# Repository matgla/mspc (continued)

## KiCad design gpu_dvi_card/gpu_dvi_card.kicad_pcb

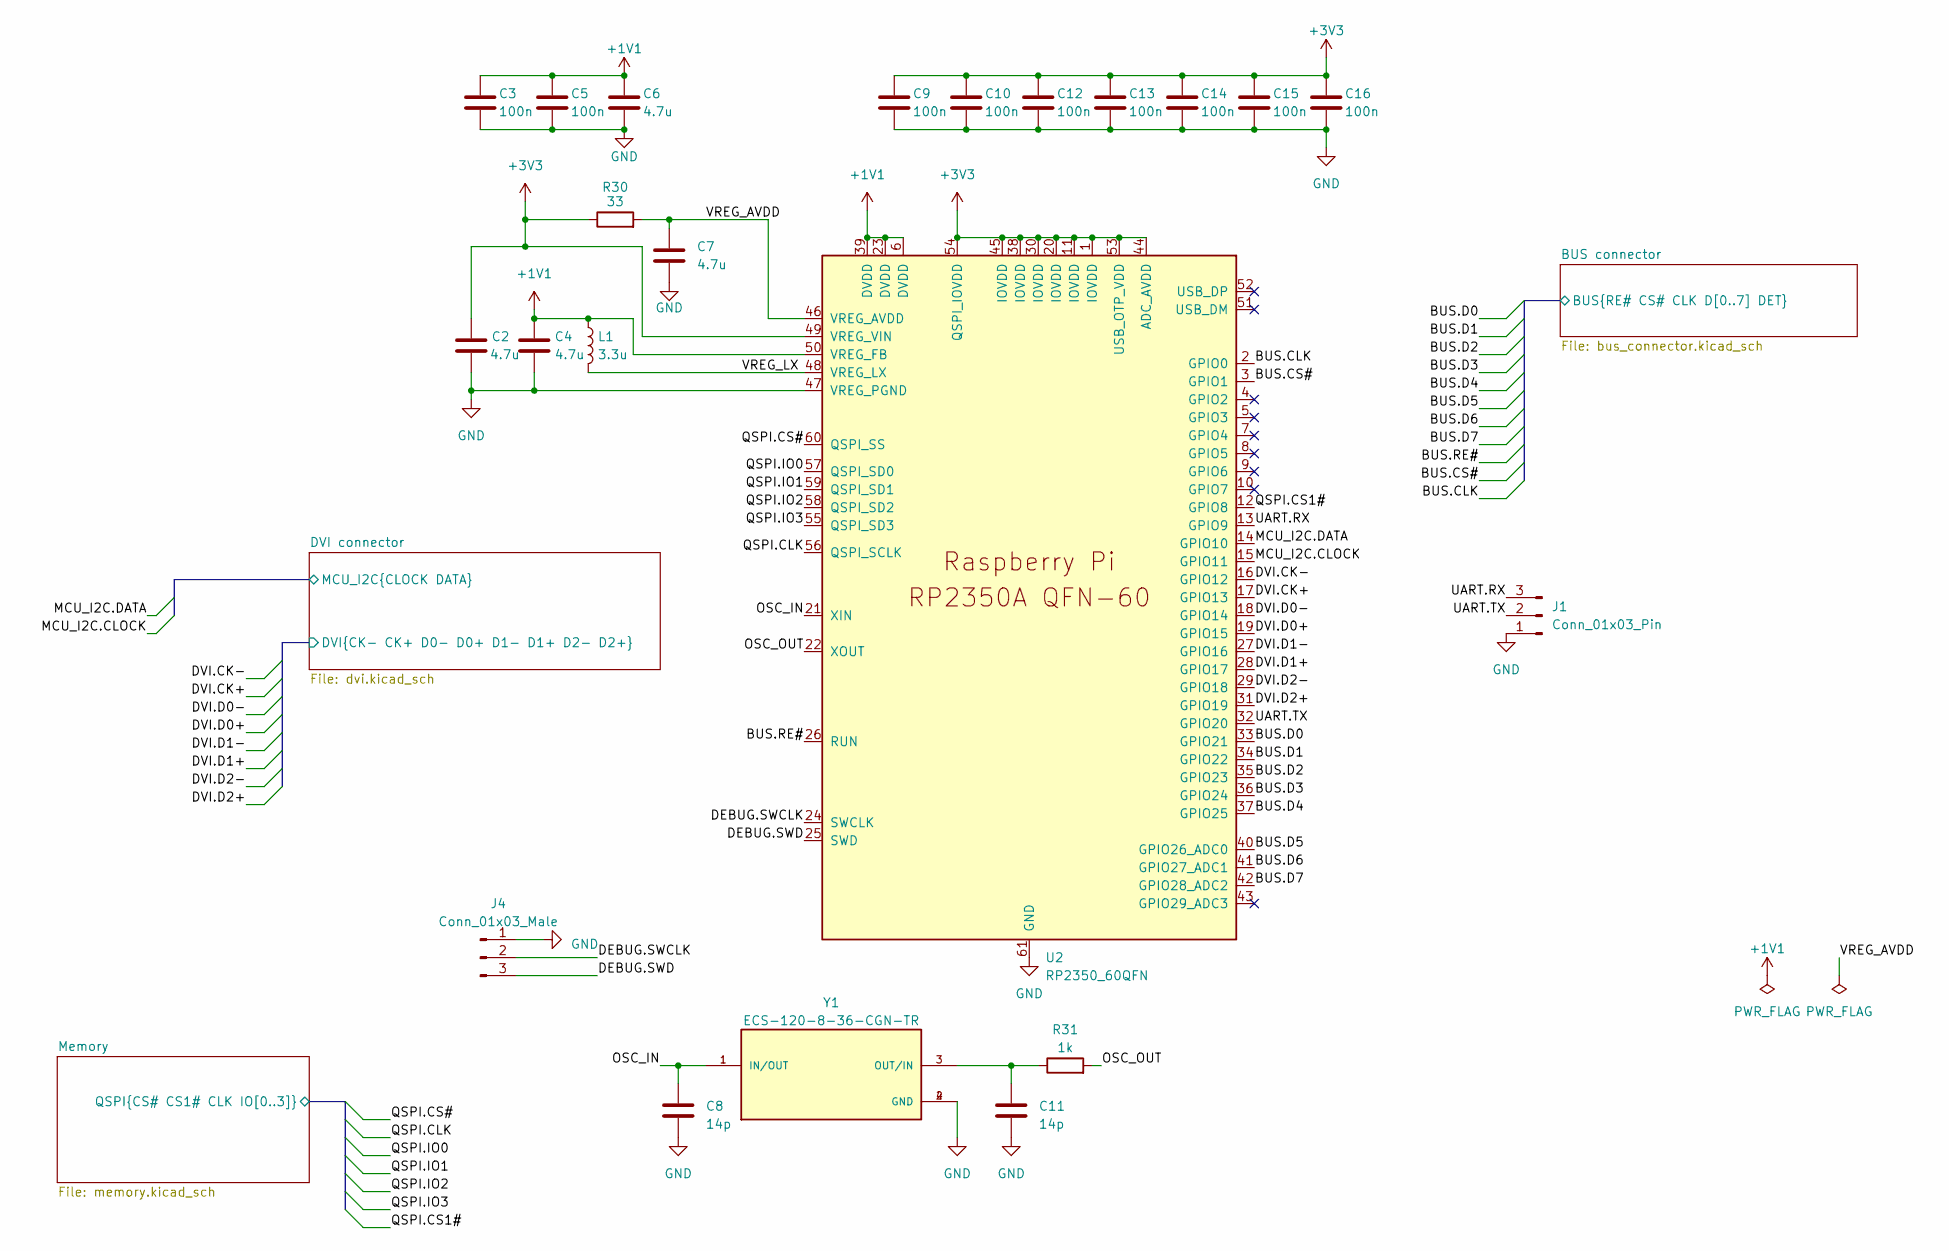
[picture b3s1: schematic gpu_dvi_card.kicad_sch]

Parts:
C2, C4, C6, C7: 4.7u; C_0402_1005Metric_Pad0.74x0.62mm_HandSolder
C3, C5, C9, C10, C12, C13, C14, C15, C16: 100n; C_0402_1005Metric_Pad0.74x0.62mm_HandSolder
C8, C11: 14p; C_0402_1005Metric_Pad0.74x0.62mm_HandSolder
J1: Conn_01x03_Pin; PinHeader_1x03_P2.54mm_Vertical
J4: Conn_01x03_Male; PinHeader_1x03_P2.54mm_Vertical
L1: 3.3u; L_0805_2012Metric_Pad1.15x1.40mm_HandSolder
R30: 33; R_0402_1005Metric_Pad0.72x0.64mm_HandSolder
R31: 1k; R_0402_1005Metric_Pad0.72x0.64mm_HandSolder
U2: RP2350_60QFN; RP2350-QFN-60-1EP_7x7_P0.4mm_EP3.4x3.4mm_ThermalVias
Y1: ECS-120-8-36-CGN-TR; XTAL_ECS-120-8-36-CGN-TR; PARTREV 2017

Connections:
+1V1: C3.1, C4.1, C5.1, C6.1, L1.1, U2.6 (DVDD), U2.23 (DVDD), U2.39 (DVDD), U2.50 (VREG_FB)
+3V3: C2.1, C9.1, C10.1, C12.1, C13.1, C14.1, C15.1, C16.1, R30.1, U2.1 (IOVDD), U2.11 (IOVDD), U2.20 (IOVDD), U2.30 (IOVDD), U2.38 (IOVDD), U2.44 (ADC_AVDD), U2.45 (IOVDD), U2.49 (VREG_VIN), U2.53 (USB_OTP_VDD), U2.54 (QSPI_IOVDD); also elsewhere on the board
/BUS connector/BUS.CLK: U2.2 (GPIO0); also elsewhere on the board
/BUS connector/BUS.CS#: U2.3 (GPIO1); also elsewhere on the board
/BUS connector/BUS.D0: U2.33 (GPIO21); also elsewhere on the board
/BUS connector/BUS.D1: U2.34 (GPIO22); also elsewhere on the board
/BUS connector/BUS.D2: U2.35 (GPIO23); also elsewhere on the board
/BUS connector/BUS.D3: U2.36 (GPIO24); also elsewhere on the board
/BUS connector/BUS.D4: U2.37 (GPIO25); also elsewhere on the board
/BUS connector/BUS.D5: U2.40 (GPIO26_ADC0); also elsewhere on the board
/BUS connector/BUS.D6: U2.41 (GPIO27_ADC1); also elsewhere on the board
/BUS connector/BUS.D7: U2.42 (GPIO28_ADC2); also elsewhere on the board
/BUS connector/BUS.RE#: U2.26 (RUN); also elsewhere on the board
/DEBUG.SWCLK: J4.2, U2.24 (SWCLK)
/DEBUG.SWD: J4.3, U2.25 (SWD)
/DVI connector/DVI.CK+: U2.17 (GPIO13); also elsewhere on the board
/DVI connector/DVI.CK-: U2.16 (GPIO12); also elsewhere on the board
/DVI connector/DVI.D0+: U2.19 (GPIO15); also elsewhere on the board
/DVI connector/DVI.D0-: U2.18 (GPIO14); also elsewhere on the board
/DVI connector/DVI.D1+: U2.28 (GPIO17); also elsewhere on the board
/DVI connector/DVI.D1-: U2.27 (GPIO16); also elsewhere on the board
/DVI connector/DVI.D2+: U2.31 (GPIO19); also elsewhere on the board
/DVI connector/DVI.D2-: U2.29 (GPIO18); also elsewhere on the board
/DVI connector/MCU_I2C.CLOCK: U2.15 (GPIO11); also elsewhere on the board
/DVI connector/MCU_I2C.DATA: U2.14 (GPIO10); also elsewhere on the board
/Memory/QSPI.CLK: U2.56 (QSPI_SCLK); also elsewhere on the board
/Memory/QSPI.CS1#: U2.12 (GPIO8); also elsewhere on the board
/Memory/QSPI.CS#: U2.60 (QSPI_SS); also elsewhere on the board
/Memory/QSPI.IO0: U2.57 (QSPI_SD0); also elsewhere on the board
/Memory/QSPI.IO1: U2.59 (QSPI_SD1); also elsewhere on the board
/Memory/QSPI.IO2: U2.58 (QSPI_SD2); also elsewhere on the board
/Memory/QSPI.IO3: U2.55 (QSPI_SD3); also elsewhere on the board
/OSC_IN: C8.1, U2.21 (XIN), Y1.1 (IN/OUT)
/OSC_OUT: R31.2, U2.22 (XOUT)
/UART.RX: J1.3, U2.13 (GPIO9)
/UART.TX: J1.2, U2.32 (GPIO20)
/VREG_AVDD: C7.1, R30.2, U2.46 (VREG_AVDD)
/VREG_LX: L1.2, U2.48 (VREG_LX)
GND: C2.2, C3.2, C4.2, C5.2, C6.2, C7.2, C8.2, C9.2, C10.2, C11.2, C12.2, C13.2, C14.2, C15.2, C16.2, J1.1, J4.1, U2.47 (VREG_PGND), U2.61 (GND), Y1.2 (GND), Y1.4 (GND); also elsewhere on the board
unnamed: C11.1, R31.1, Y1.3 (OUT/IN)

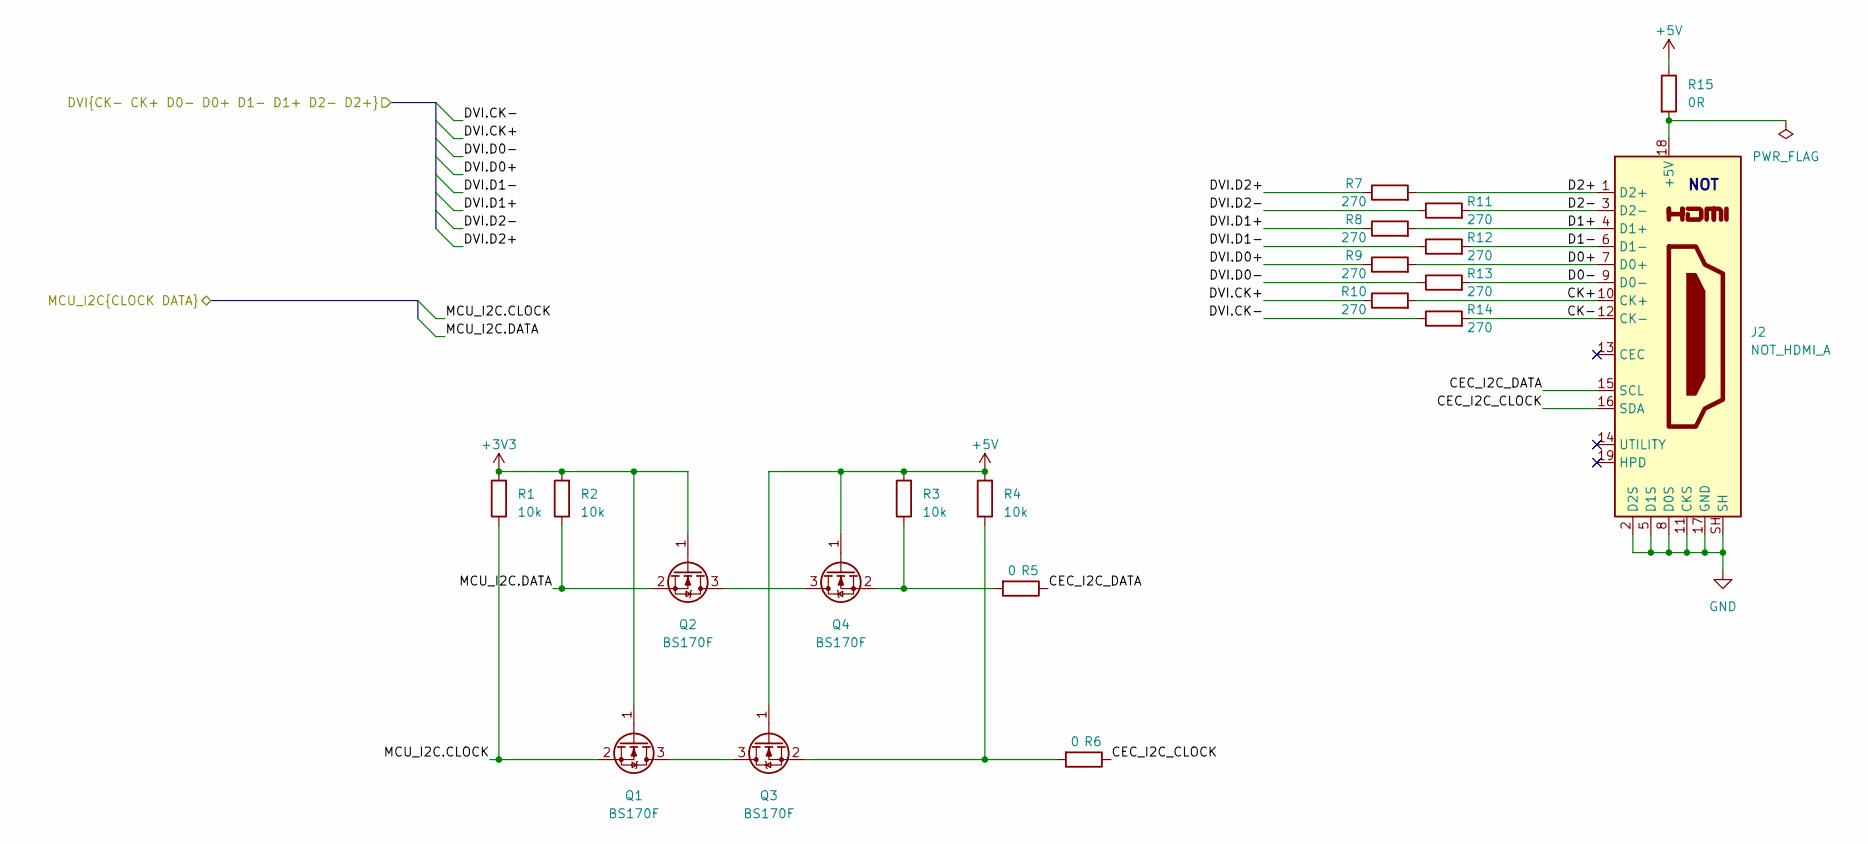
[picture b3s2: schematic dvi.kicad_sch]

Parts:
J2: NOT_HDMI_A; HDMI_A_Molex_208658-1001_Horizontal
Q1, Q2, Q3, Q4: BS170F; SOT-23
R1, R2, R3, R4: 10k; R_0402_1005Metric_Pad0.72x0.64mm_HandSolder
R5, R6: 0; R_0402_1005Metric_Pad0.72x0.64mm_HandSolder
R7, R8, R9, R10, R11, R12, R13, R14: 270; R_0402_1005Metric_Pad0.72x0.64mm_HandSolder
R15: 0R; R_0402_1005Metric_Pad0.72x0.64mm_HandSolder

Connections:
+3V3: Q1.1 (G), Q2.1 (G), R1.2, R2.2; also elsewhere on the board
+5V: Q3.1 (G), Q4.1 (G), R3.2, R4.2, R15.1; also elsewhere on the board
/DVI connector/CEC_I2C_CLOCK: J2.16 (SDA), R6.1
/DVI connector/CEC_I2C_DATA: J2.15 (SCL), R5.1
/DVI connector/CK+: J2.10 (CK+), R10.2
/DVI connector/CK-: J2.12 (CK-), R14.2
/DVI connector/D0+: J2.7 (D0+), R9.2
/DVI connector/D0-: J2.9 (D0-), R13.2
/DVI connector/D1+: J2.4 (D1+), R8.2
/DVI connector/D1-: J2.6 (D1-), R12.2
/DVI connector/D2+: J2.1 (D2+), R7.2
/DVI connector/D2-: J2.3 (D2-), R11.2
/DVI connector/DVI.CK+: R10.1; also elsewhere on the board
/DVI connector/DVI.CK-: R14.1; also elsewhere on the board
/DVI connector/DVI.D0+: R9.1; also elsewhere on the board
/DVI connector/DVI.D0-: R13.1; also elsewhere on the board
/DVI connector/DVI.D1+: R8.1; also elsewhere on the board
/DVI connector/DVI.D1-: R12.1; also elsewhere on the board
/DVI connector/DVI.D2+: R7.1; also elsewhere on the board
/DVI connector/DVI.D2-: R11.1; also elsewhere on the board
/DVI connector/MCU_I2C.CLOCK: Q1.2 (S), R1.1; also elsewhere on the board
/DVI connector/MCU_I2C.DATA: Q2.2 (S), R2.1; also elsewhere on the board
GND: J2.2 (D2S), J2.5 (D1S), J2.8 (D0S), J2.11 (CKS), J2.17 (GND), J2.SH; also elsewhere on the board
unnamed: J2.18 (+5V), R15.2
unnamed: Q1.3 (D), Q3.3 (D)
unnamed: Q2.3 (D), Q4.3 (D)
unnamed: Q3.2 (S), R4.1, R6.2
unnamed: Q4.2 (S), R3.1, R5.2

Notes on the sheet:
NOT

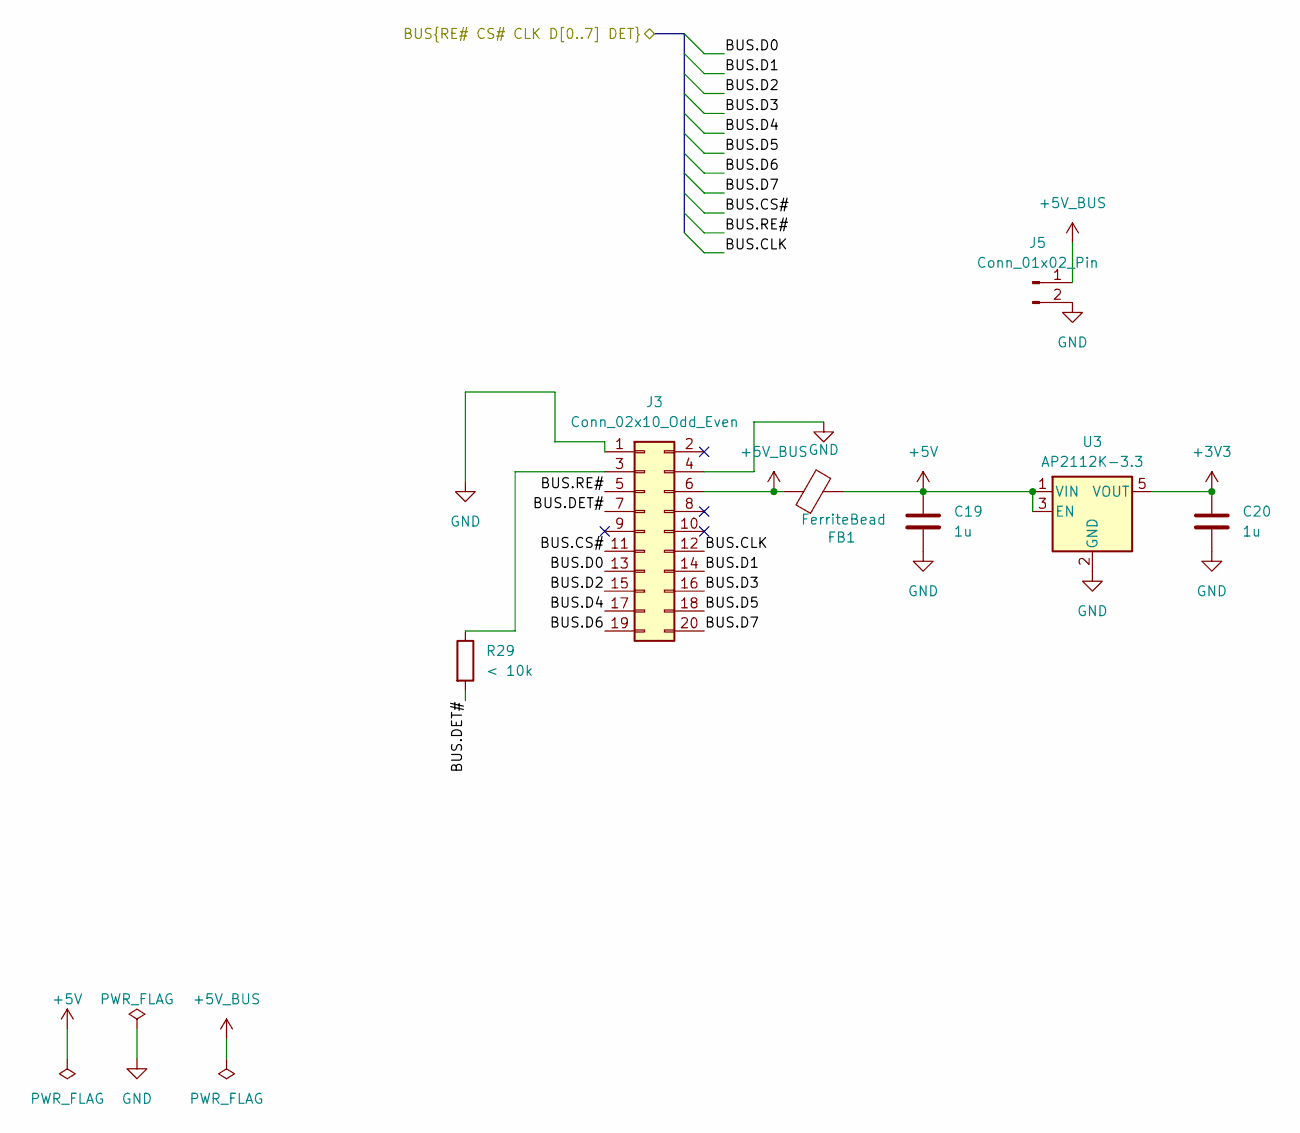
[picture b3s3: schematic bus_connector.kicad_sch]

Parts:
C19, C20: 1u; C_0402_1005Metric_Pad0.74x0.62mm_HandSolder
FB1: FerriteBead; L_0805_2012Metric_Pad1.05x1.20mm_HandSolder
J3: Conn_02x10_Odd_Even; PinHeader_2x10_P1.27mm_Vertical_SMD
J5: Conn_01x02_Pin; PinHeader_1x02_P2.54mm_Vertical
R29: < 10k; R_0402_1005Metric_Pad0.72x0.64mm_HandSolder
U3: AP2112K-3.3; SOT-23-5_HandSoldering

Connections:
+3V3: C20.1, U3.5 (VOUT); also elsewhere on the board
+5V: C19.1, FB1.2, U3.1 (VIN), U3.3 (EN); also elsewhere on the board
+5V_BUS: FB1.1, J3.6, J5.1
/BUS connector/BUS.CLK: J3.12; also elsewhere on the board
/BUS connector/BUS.CS#: J3.11; also elsewhere on the board
/BUS connector/BUS.D0: J3.13; also elsewhere on the board
/BUS connector/BUS.D1: J3.14; also elsewhere on the board
/BUS connector/BUS.D2: J3.15; also elsewhere on the board
/BUS connector/BUS.D3: J3.16; also elsewhere on the board
/BUS connector/BUS.D4: J3.17; also elsewhere on the board
/BUS connector/BUS.D5: J3.18; also elsewhere on the board
/BUS connector/BUS.D6: J3.19; also elsewhere on the board
/BUS connector/BUS.D7: J3.20; also elsewhere on the board
/BUS connector/BUS.DET#: J3.7, R29.2
/BUS connector/BUS.RE#: J3.5; also elsewhere on the board
GND: C19.2, C20.2, J3.1, J3.4, J5.2, U3.2 (GND); also elsewhere on the board
unnamed: J3.3, R29.1

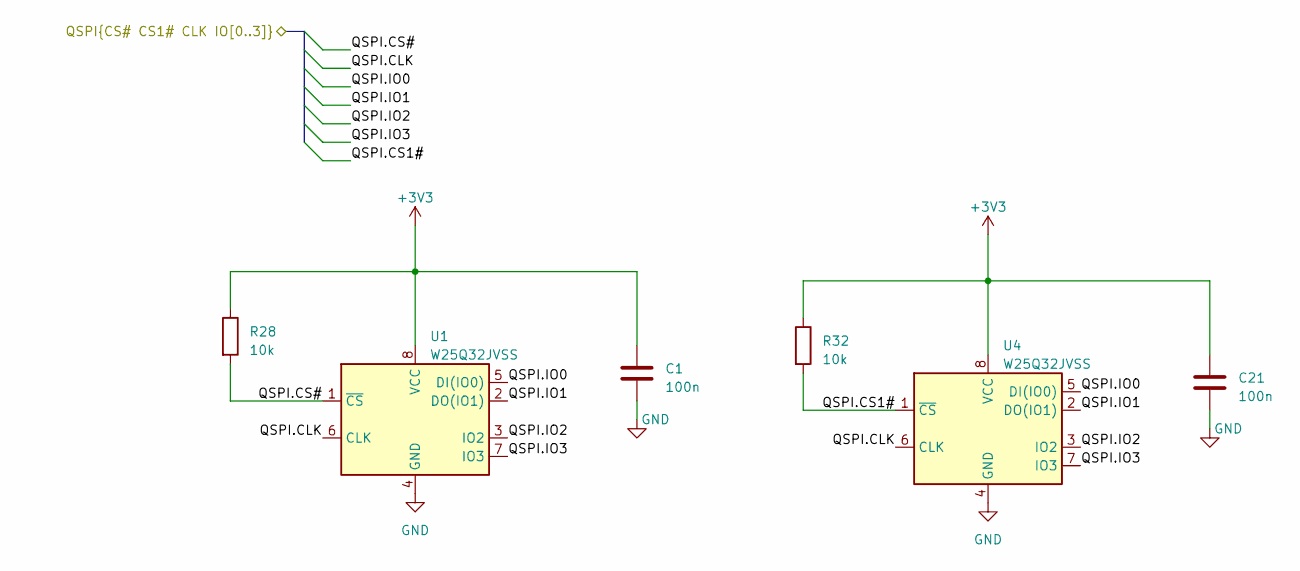
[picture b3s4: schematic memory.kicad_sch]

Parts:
C1, C21: 100n; C_0402_1005Metric_Pad0.74x0.62mm_HandSolder
R28, R32: 10k; R_0402_1005Metric_Pad0.72x0.64mm_HandSolder
U1, U4: W25Q32JVSS; SOIC-8_5.23x5.23mm_P1.27mm

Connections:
+3V3: C1.1, C21.1, R28.1, R32.1, U1.8 (VCC), U4.8 (VCC); also elsewhere on the board
/Memory/QSPI.CLK: U1.6 (CLK), U4.6 (CLK); also elsewhere on the board
/Memory/QSPI.CS1#: R32.2, U4.1 (~CS); also elsewhere on the board
/Memory/QSPI.CS#: R28.2, U1.1 (~CS); also elsewhere on the board
/Memory/QSPI.IO0: U1.5 (DI(IO0)), U4.5 (DI(IO0)); also elsewhere on the board
/Memory/QSPI.IO1: U1.2 (DO(IO1)), U4.2 (DO(IO1)); also elsewhere on the board
/Memory/QSPI.IO2: U1.3 (IO2), U4.3 (IO2); also elsewhere on the board
/Memory/QSPI.IO3: U1.7 (IO3), U4.7 (IO3); also elsewhere on the board
GND: C1.2, C21.2, U1.4 (GND), U4.4 (GND); also elsewhere on the board

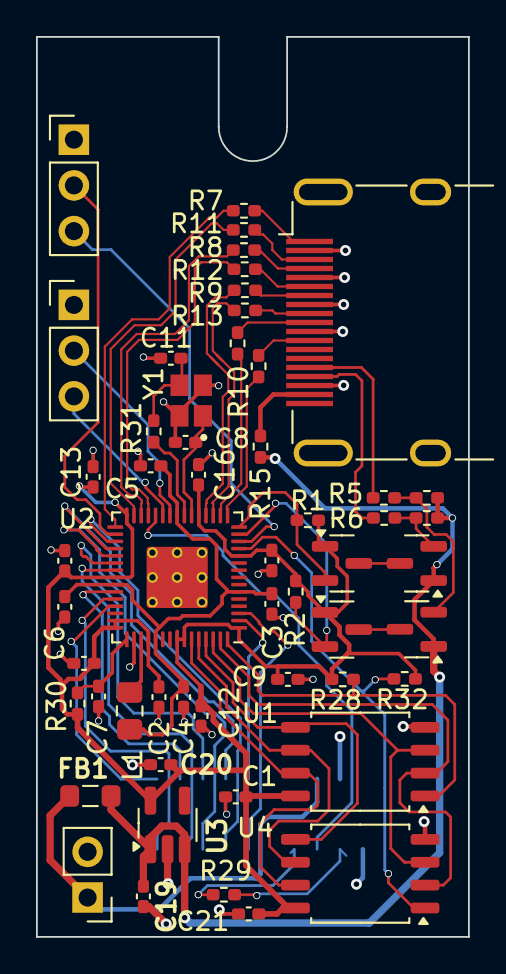
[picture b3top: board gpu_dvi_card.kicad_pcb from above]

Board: 4 copper layers, 24.0 x 50.0 mm, 55 parts (1 on the bottom side), 59 nets.

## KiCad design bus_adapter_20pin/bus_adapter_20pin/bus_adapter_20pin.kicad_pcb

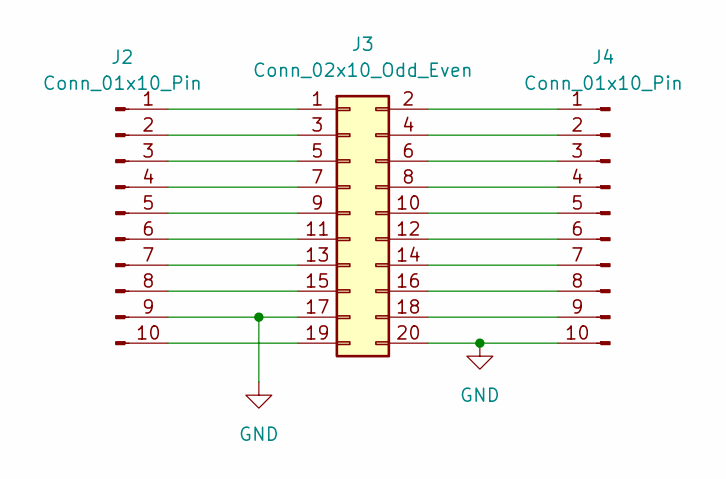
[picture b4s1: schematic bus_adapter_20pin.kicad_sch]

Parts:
J2, J4: Conn_01x10_Pin; PinHeader_1x10_P2.54mm_Vertical
J3: Conn_02x10_Odd_Even; PinHeader_2x10_P1.27mm_Vertical_SMD

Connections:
GND: J2.9, J3.17, J3.20, J4.10
unnamed: J2.1, J3.1
unnamed: J2.2, J3.3
unnamed: J2.3, J3.5
unnamed: J2.4, J3.7
unnamed: J2.5, J3.9
unnamed: J2.6, J3.11
unnamed: J2.7, J3.13
unnamed: J2.8, J3.15
unnamed: J2.10, J3.19
unnamed: J3.2, J4.1
unnamed: J3.4, J4.2
unnamed: J3.6, J4.3
unnamed: J3.8, J4.4
unnamed: J3.10, J4.5
unnamed: J3.12, J4.6
unnamed: J3.14, J4.7
unnamed: J3.16, J4.8
unnamed: J3.18, J4.9

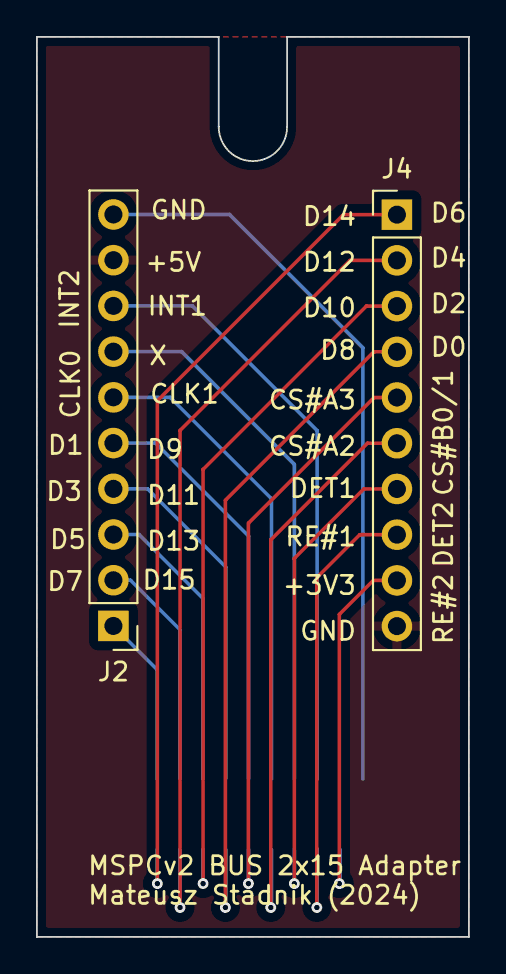
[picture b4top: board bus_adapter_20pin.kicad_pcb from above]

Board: 2 copper layers, 24.0 x 50.0 mm, 3 parts (1 on the bottom side), 19 nets.

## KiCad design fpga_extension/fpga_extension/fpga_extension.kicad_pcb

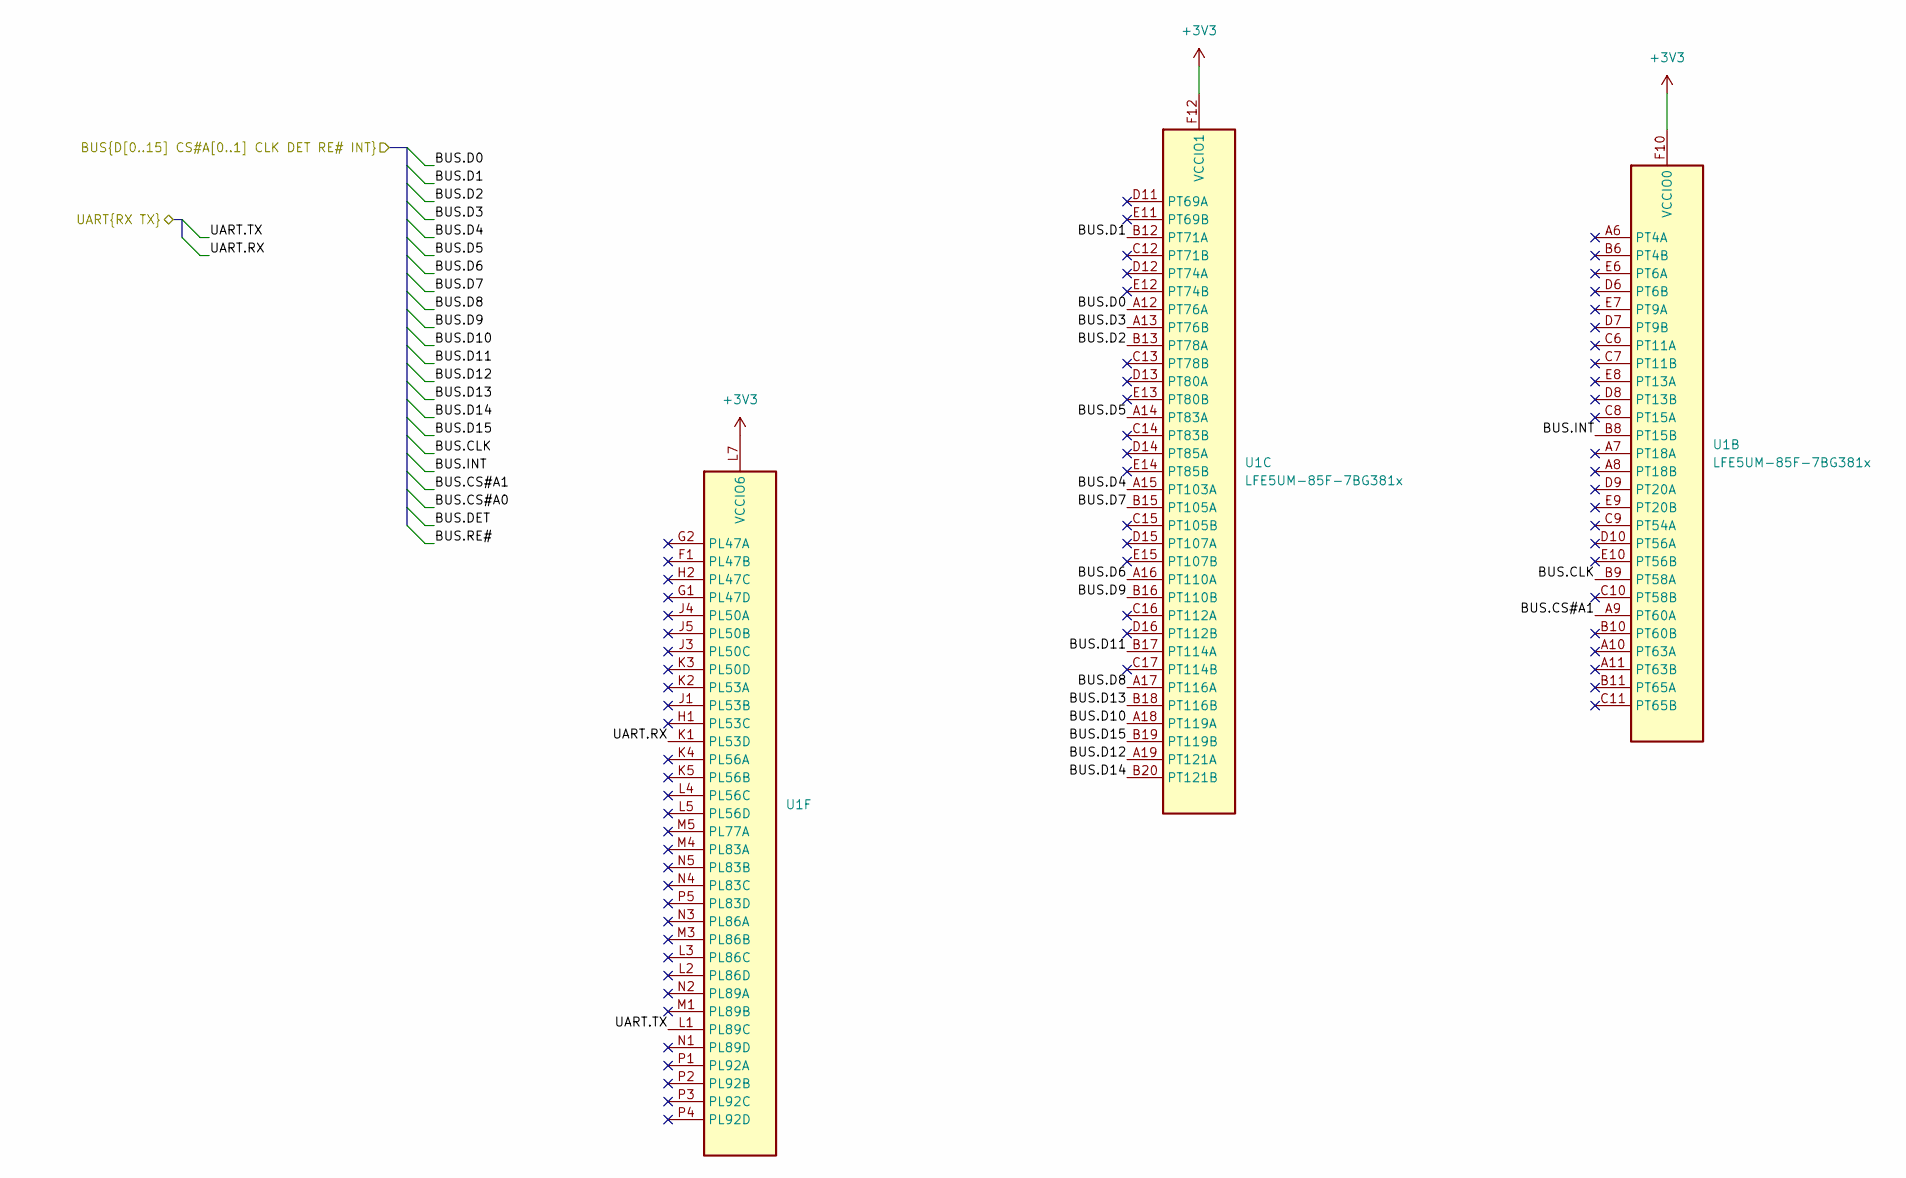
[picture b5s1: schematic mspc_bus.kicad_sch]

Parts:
U1: LFE5UM-85F-7BG381x; Lattice_caBGA-381_17.0x17.0mm_Layout20x20_P0.8mm_Ball0.4mm_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

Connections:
+3V3: U1.F9 (VCCIO0), U1.F10 (VCCIO0), U1.F11 (VCCIO1), U1.F12 (VCCIO1), U1.L6 (VCCIO6), U1.L7 (VCCIO6), U1.M6 (VCCIO6); also elsewhere on the board
/Connector/BUS.CLK: U1.B9 (PT58A); also elsewhere on the board
/Connector/BUS.CS#A1: U1.A9 (PT60A); also elsewhere on the board
/Connector/BUS.D0: U1.A12 (PT76A); also elsewhere on the board
/Connector/BUS.D1: U1.B12 (PT71A); also elsewhere on the board
/Connector/BUS.D2: U1.B13 (PT78A); also elsewhere on the board
/Connector/BUS.D3: U1.A13 (PT76B); also elsewhere on the board
/Connector/BUS.D4: U1.A15 (PT103A); also elsewhere on the board
/Connector/BUS.D5: U1.A14 (PT83A); also elsewhere on the board
/Connector/BUS.D6: U1.A16 (PT110A); also elsewhere on the board
/Connector/BUS.D7: U1.B15 (PT105A); also elsewhere on the board
/Connector/BUS.D8: U1.A17 (PT116A); also elsewhere on the board
/Connector/BUS.D9: U1.B16 (PT110B); also elsewhere on the board
/Connector/BUS.D10: U1.A18 (PT119A); also elsewhere on the board
/Connector/BUS.D11: U1.B17 (PT114A); also elsewhere on the board
/Connector/BUS.D12: U1.A19 (PT121A); also elsewhere on the board
/Connector/BUS.D13: U1.B18 (PT116B); also elsewhere on the board
/Connector/BUS.D14: U1.B20 (PT121B); also elsewhere on the board
/Connector/BUS.D15: U1.B19 (PT119B); also elsewhere on the board
/Connector/BUS.INT: U1.B8 (PT15B); also elsewhere on the board
/JTAG/UART.RX: U1.K1 (PL53D); also elsewhere on the board
/JTAG/UART.TX: U1.L1 (PL89C); also elsewhere on the board

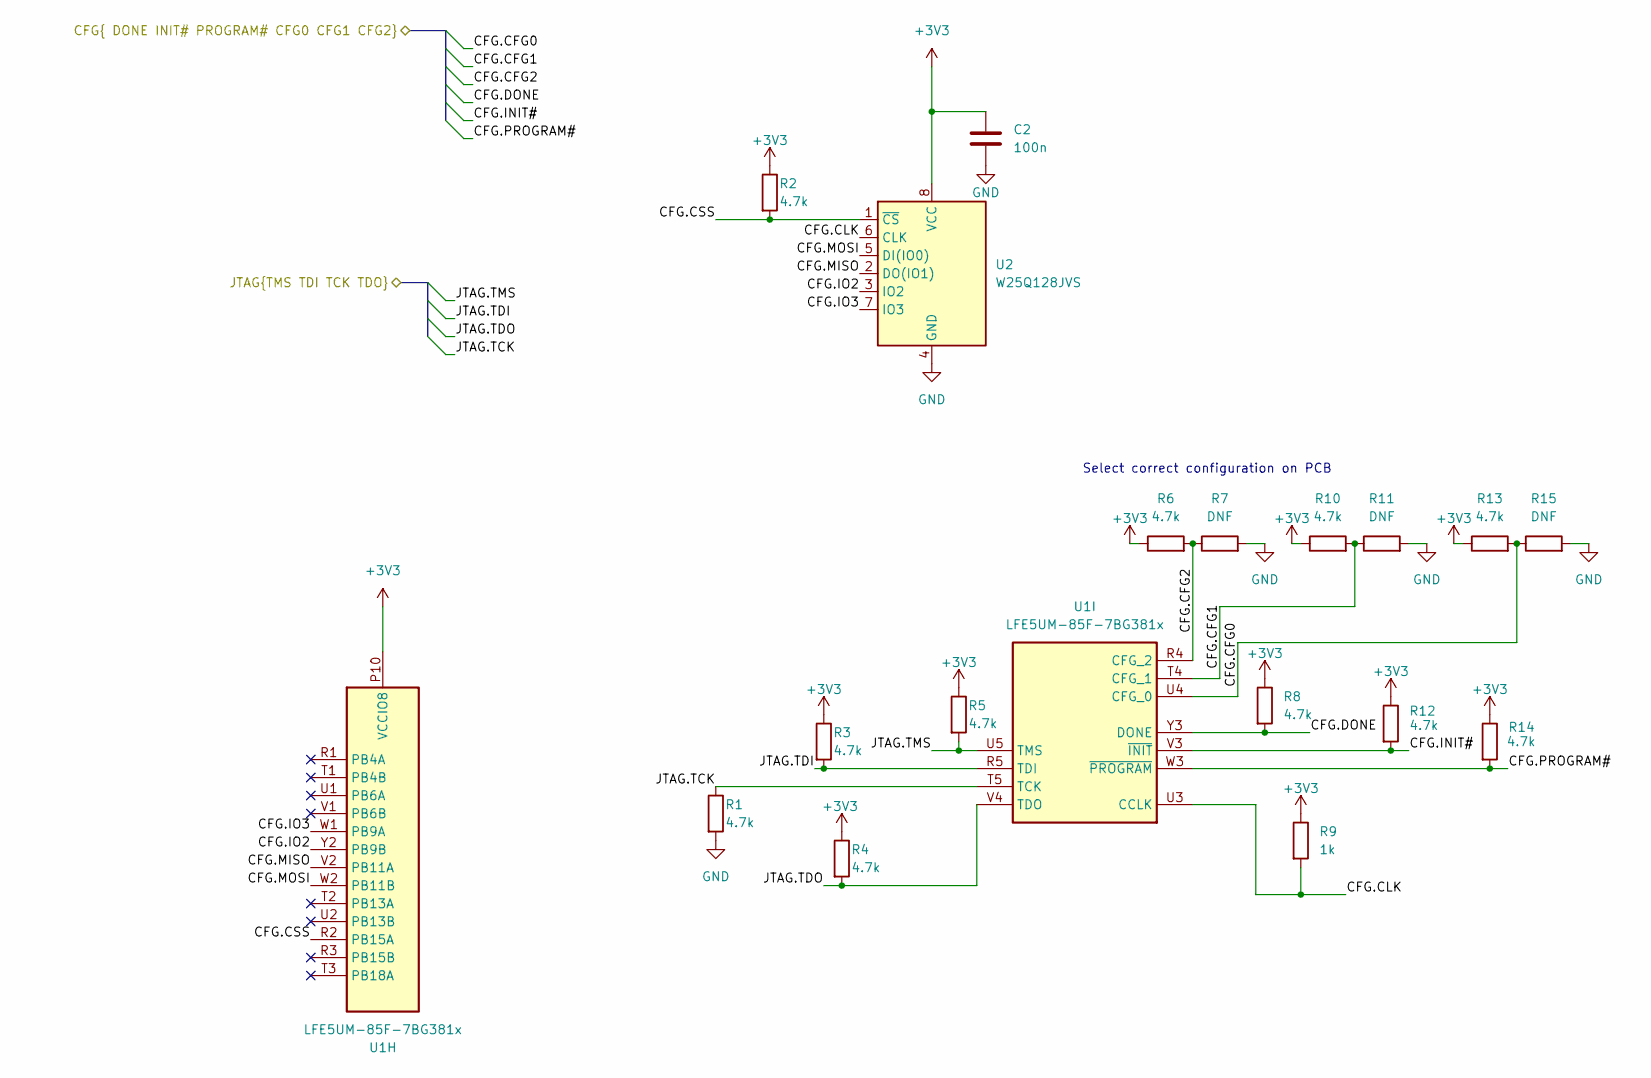
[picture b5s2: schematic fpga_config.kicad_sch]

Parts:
C2: 100n; C_0402_1005Metric_Pad0.74x0.62mm_HandSolder
R1, R2, R3, R4, R5, R6, R8, R10, R12, R13, R14: 4.7k; R_0402_1005Metric_Pad0.72x0.64mm_HandSolder
R7, R11, R15: DNF; R_0402_1005Metric_Pad0.72x0.64mm_HandSolder
R9: 1k; R_0402_1005Metric_Pad0.72x0.64mm_HandSolder
U1: LFE5UM-85F-7BG381x; Lattice_caBGA-381_17.0x17.0mm_Layout20x20_P0.8mm_Ball0.4mm_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
U2: W25Q128JVS; SOIC-8_5.23x5.23mm_P1.27mm

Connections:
+3V3: C2.1, R2.1, R3.1, R4.1, R5.1, R6.1, R8.1, R9.1, R10.1, R12.1, R13.1, R14.1, U1.P9 (VCCIO8), U1.P10 (VCCIO8), U2.8 (VCC); also elsewhere on the board
/FPGA Configuration/CFG.CFG0: R13.2, R15.1, U1.U4 (CFG_0); also elsewhere on the board
/FPGA Configuration/CFG.CFG1: R10.2, R11.1, U1.T4 (CFG_1); also elsewhere on the board
/FPGA Configuration/CFG.CFG2: R6.2, R7.1, U1.R4 (CFG_2); also elsewhere on the board
/FPGA Configuration/CFG.CLK: R9.2, U1.U3 (CCLK), U2.6 (CLK)
/FPGA Configuration/CFG.CSS: R2.2, U1.R2 (PB15A), U2.1 (~CS)
/FPGA Configuration/CFG.DONE: R8.2, U1.Y3 (DONE); also elsewhere on the board
/FPGA Configuration/CFG.INIT#: R12.2, U1.V3 (~INIT); also elsewhere on the board
/FPGA Configuration/CFG.IO2: U1.Y2 (PB9B), U2.3 (IO2)
/FPGA Configuration/CFG.IO3: U1.W1 (PB9A), U2.7 (IO3)
/FPGA Configuration/CFG.MISO: U1.V2 (PB11A), U2.2 (DO(IO1))
/FPGA Configuration/CFG.MOSI: U1.W2 (PB11B), U2.5 (DI(IO0))
/FPGA Configuration/CFG.PROGRAM#: R14.2, U1.W3 (~PROGRAM); also elsewhere on the board
/FPGA Configuration/JTAG.TCK: R1.1, U1.T5 (TCK); also elsewhere on the board
/FPGA Configuration/JTAG.TDI: R3.2, U1.R5 (TDI); also elsewhere on the board
/FPGA Configuration/JTAG.TDO: R4.2, U1.V4 (TDO); also elsewhere on the board
/FPGA Configuration/JTAG.TMS: R5.2, U1.U5 (TMS); also elsewhere on the board
GND: C2.2, R1.2, R7.2, R11.2, R15.2, U2.4 (GND); also elsewhere on the board

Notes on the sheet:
Select correct configuration on PCB

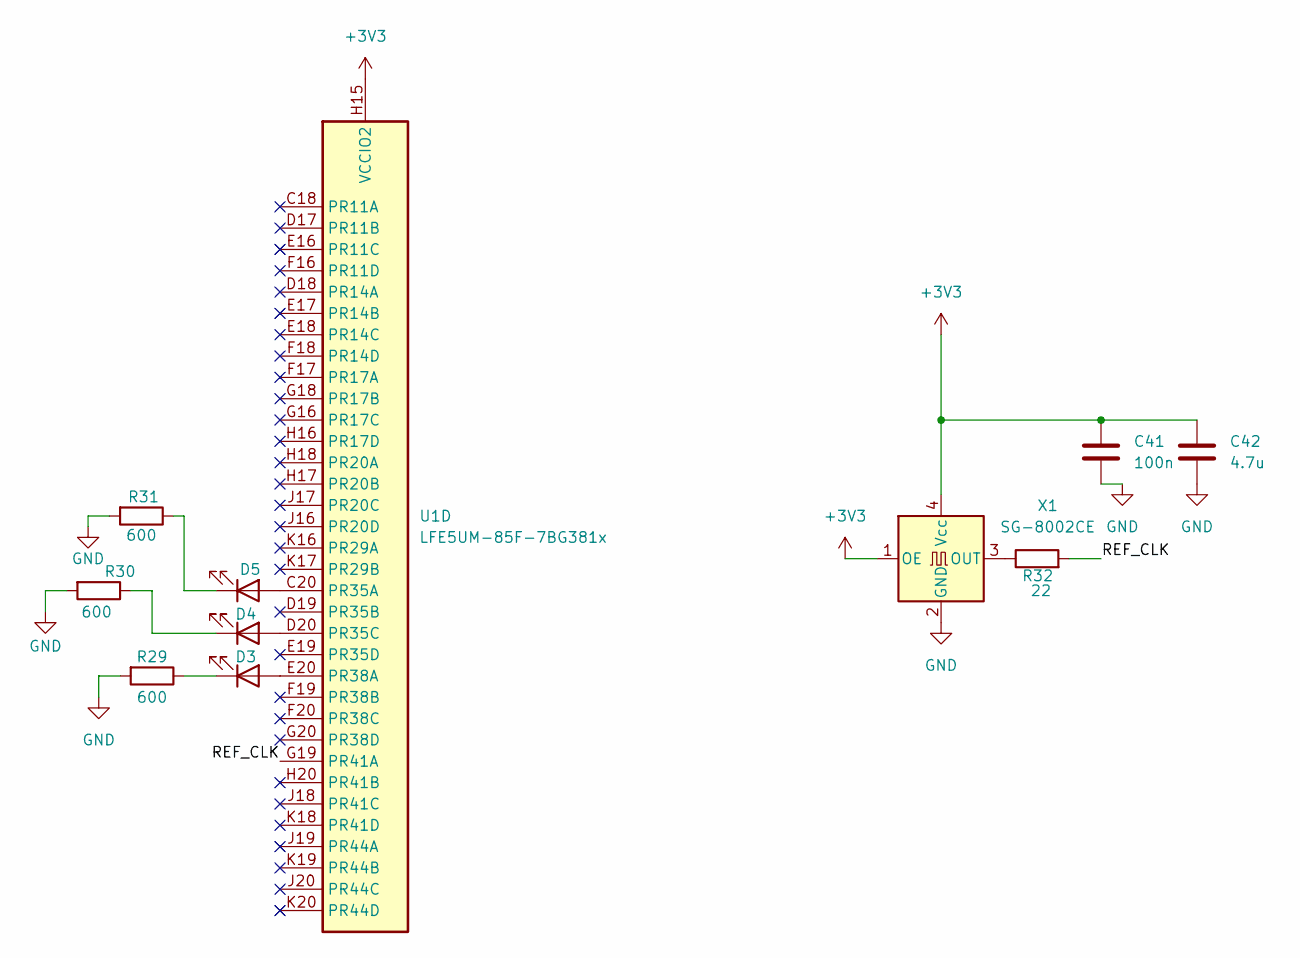
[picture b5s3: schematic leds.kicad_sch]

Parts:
C41: 100n; C_0402_1005Metric_Pad0.74x0.62mm_HandSolder
C42: 4.7u; C_0402_1005Metric_Pad0.74x0.62mm_HandSolder
D3, D4, D5: LED; LED_0402_1005Metric_Pad0.77x0.64mm_HandSolder
R29, R30, R31: 600; R_0402_1005Metric_Pad0.72x0.64mm_HandSolder
R32: 22; R_0402_1005Metric_Pad0.72x0.64mm_HandSolder
U1: LFE5UM-85F-7BG381x; Lattice_caBGA-381_17.0x17.0mm_Layout20x20_P0.8mm_Ball0.4mm_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
X1: SG-8002CE; Oscillator_SMD_SeikoEpson_SG210-4Pin_2.5x2.0mm

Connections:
+3V3: C41.1, C42.1, U1.H14 (VCCIO2), U1.H15 (VCCIO2), U1.J15 (VCCIO2), X1.1 (OE), X1.4 (Vcc); also elsewhere on the board
/LEDs/REF_CLK: R32.2, U1.G19 (PR41A)
GND: C41.2, C42.2, R29.2, R30.2, R31.2, X1.2 (GND); also elsewhere on the board
unnamed: D3.2 (A), U1.E20 (PR38A)
unnamed: D3.1 (K), R29.1
unnamed: D4.2 (A), U1.D20 (PR35C)
unnamed: D4.1 (K), R30.1
unnamed: D5.2 (A), U1.C20 (PR35A)
unnamed: D5.1 (K), R31.1
unnamed: R32.1, X1.3 (OUT)
